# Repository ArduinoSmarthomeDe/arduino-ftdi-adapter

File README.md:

# FTDI Adapter -> Arduino Molex PicoBlade

## Description

Small adapter board to simply connect a regular FTDI programmer (USB) to a Molex Picoblade FTDI socket (such as  used on the [Arduino Nano Cased](https://github.com/ArduinoSmarthomeDe/arduino-nano-cased)). Needs a 1.25mm PicoBlade cable with cross connection pins.

## Preview

## Layout & Production 

You can find all the open data here as a [KiCad](http://kicad.github.io) project. The *Gerber files* for the production of the board can be found here under **releases**.

## License

The MIT License (MIT)

Copyright (c) 2021 André Husken hello@arduino-smarthome.de

Permission is hereby granted, free of charge, to any person obtaining a copy of this software and associated documentation files (the "Software"), to deal in the Software without restriction, including without limitation the rights to use, copy, modify, merge, publish, distribute, sublicense, and/or sell copies of the Software, and to permit persons to whom the Software is furnished to do so, subject to the following conditions:

The above copyright notice and this permission notice shall be included in all copies or substantial portions of the Software.

THE SOFTWARE IS PROVIDED "AS IS", WITHOUT WARRANTY OF ANY KIND, EXPRESS OR IMPLIED, INCLUDING BUT NOT LIMITED TO THE WARRANTIES OF MERCHANTABILITY, FITNESS FOR A PARTICULAR PURPOSE AND NONINFRINGEMENT. IN NO EVENT SHALL THE AUTHORS OR COPYRIGHT HOLDERS BE LIABLE FOR ANY CLAIM, DAMAGES OR OTHER LIABILITY, WHETHER IN AN ACTION OF CONTRACT, TORT OR OTHERWISE, ARISING FROM, OUT OF OR IN CONNECTION WITH THE SOFTWARE OR THE USE OR OTHER DEALINGS IN THE SOFTWARE.

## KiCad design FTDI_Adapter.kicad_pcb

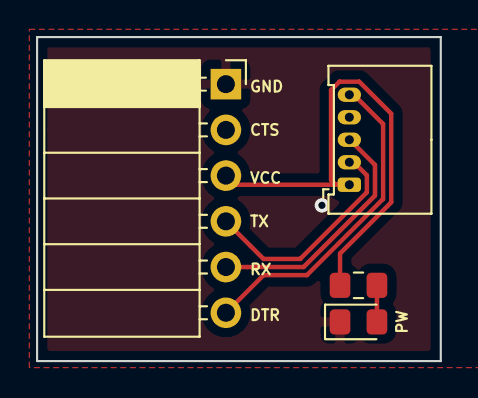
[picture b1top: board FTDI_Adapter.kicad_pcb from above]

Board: 2 copper layers, 22.4 x 18.0 mm, 4 parts (0 on the bottom side), 6 nets.

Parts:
D1: PW; LED_0805_2012Metric_Pad1.15x1.40mm_HandSolder
J1: Conn_01x06_Female; PinSocket_1x06_P2.54mm_Horizontal
J2: Conn_01x05_Female; Molex_PicoBlade_53048-0510_1x05_P1.25mm_Horizontal
R1: 220; R_0805_2012Metric_Pad1.15x1.40mm_HandSolder

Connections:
DTR: J1.6, J2.5
GND: D1.1, J1.1, J2.4
unnamed: D1.2, R1.2
RX: J1.5, J2.3
TX: J1.4, J2.2
VCC: J1.3, J2.1, R1.1

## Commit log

2021-09-08 V.1.0
2021-09-08 readme, preview
2021-09-08 readme

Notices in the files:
FTDI_Adapter.kicad_pcb:
© André Husken | V.1.0
